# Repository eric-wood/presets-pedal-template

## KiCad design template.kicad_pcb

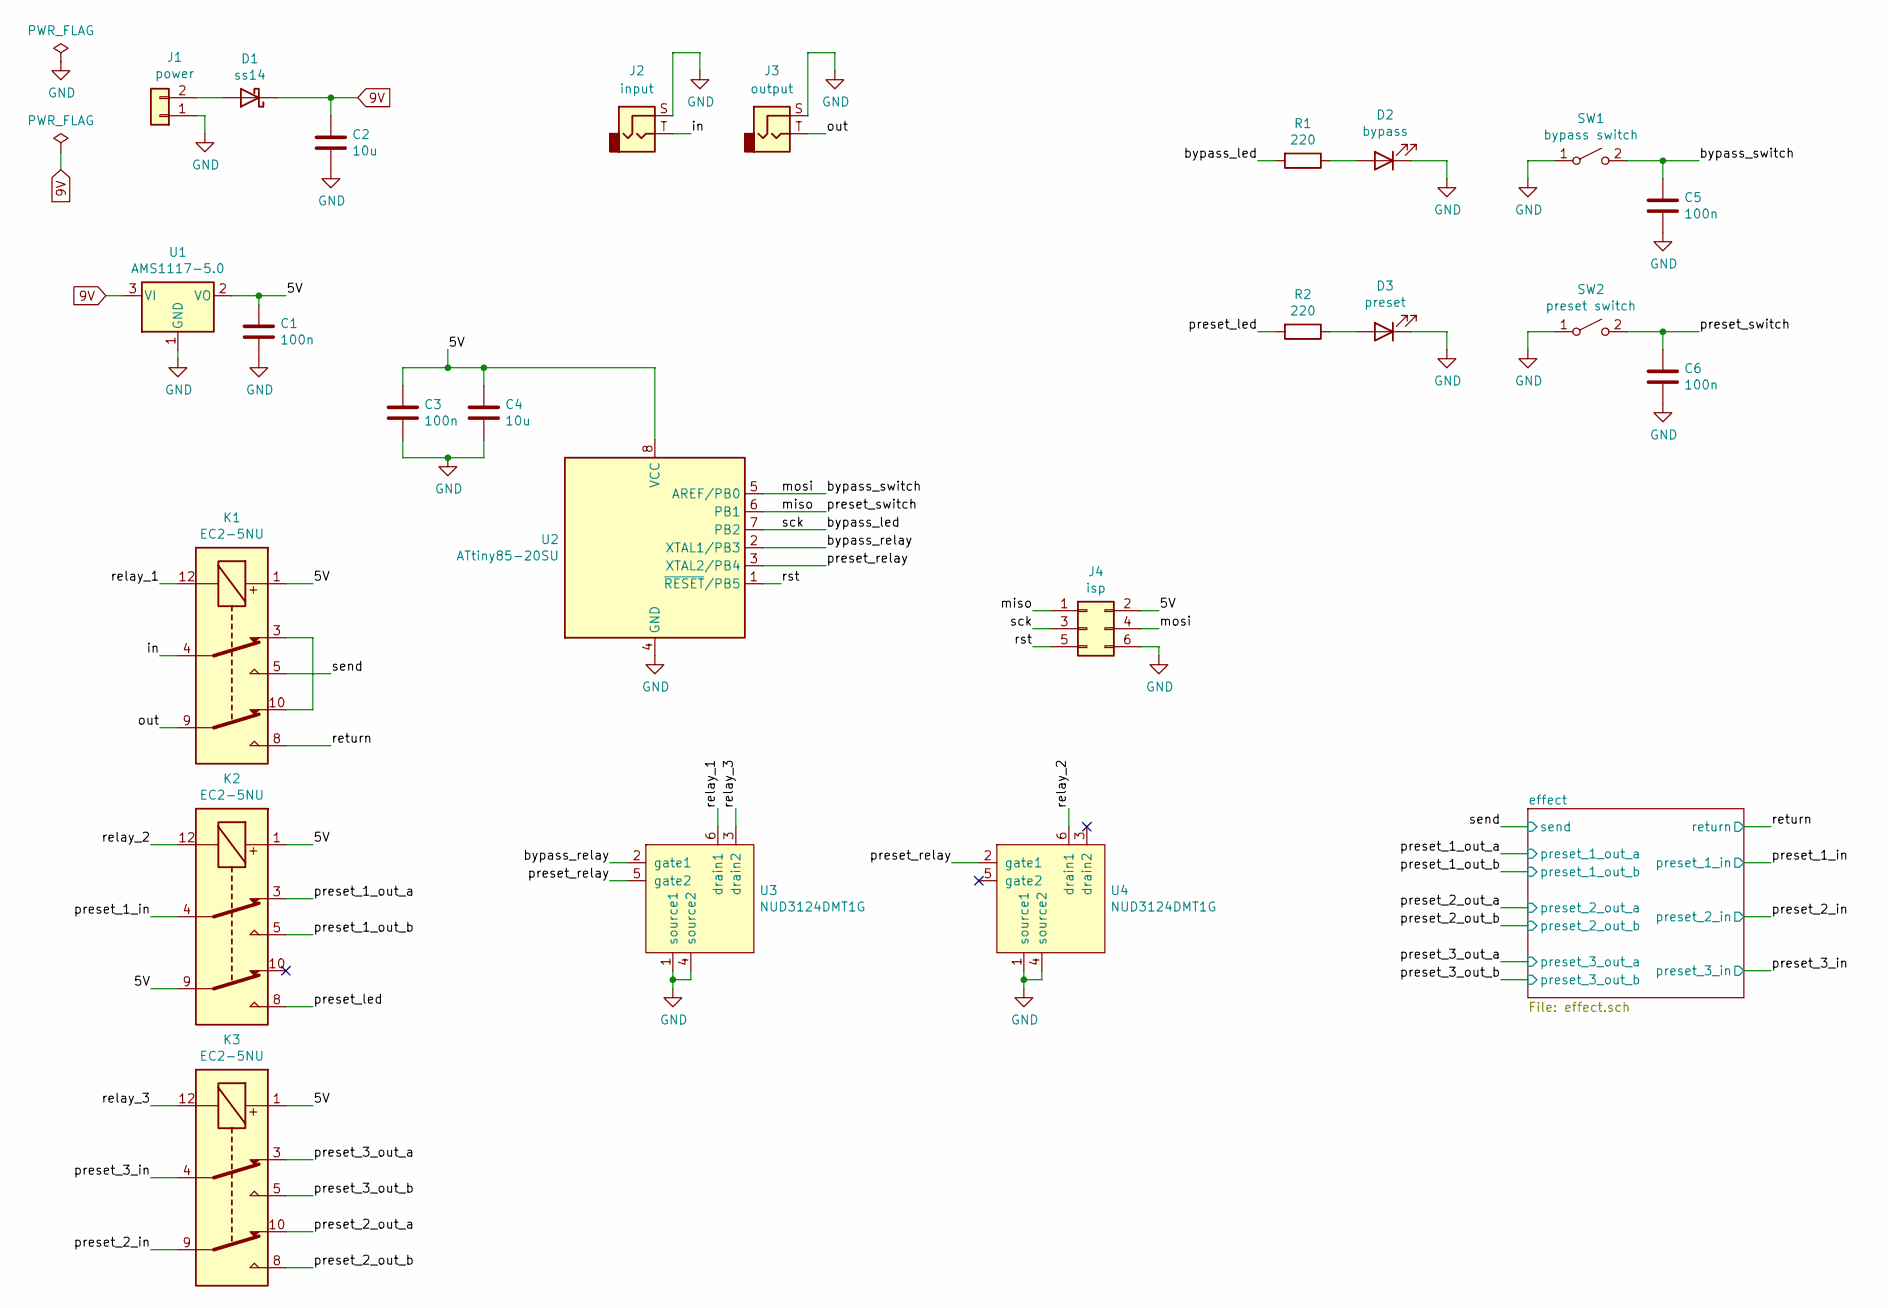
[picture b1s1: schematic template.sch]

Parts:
C1, C3, C5, C6: 100n; C_0603_1608Metric; LCSC C14663
C2, C4: 10u; C_1206_3216Metric; LCSC C13585
D1: ss14; D_SMA; LCSC C2480
D2: bypass; LED_D5.0mm_compact
D3: preset; LED_D5.0mm_compact
J1: power; PinHeader_1x02_P2.54mm_Vertical
J2: input; Jack_6.35mm_Neutrik_NMJ4HCD2_Horizontal
J3: output; Jack_6.35mm_Neutrik_NMJ4HCD2_Horizontal
J4: isp; PinHeader_2x03_P2.54mm_Vertical
K1, K2, K3: EC2-5NU; Relay_DPDT_Kemet_EC2
R1, R2: 220; R_0603_1608Metric; LCSC C22962
SW1: bypass switch; JST_XH_B2B-XH-A_1x02_P2.50mm_Vertical
SW2: preset switch; JST_XH_B2B-XH-A_1x02_P2.50mm_Vertical
U1: AMS1117-5.0; SOT-223-3_TabPin2; LCSC C6187
U2: ATtiny85-20SU; SOIJ-8_5.3x5.3mm_P1.27mm
U3, U4: NUD3124DMT1G; SC-74-6_1.5x2.9mm_P0.95mm

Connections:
9V: C2.1, D1.1 (K), U1.3 (VI); also elsewhere on the board
/5V: C1.1, C3.1, C4.1, J4.2, K1.1, K2.1, K2.9, K3.1, U1.2 (VO), U2.8 (VCC)
/bypass_led: J4.3, R1.2, U2.7 (PB2)
/bypass_relay: U2.2 (XTAL1/PB3), U3.2 (gate1)
/bypass_switch: C5.1, J4.4, SW1.2 (B), U2.5 (AREF/PB0)
/in: J2.T, K1.4
/miso: C6.1, J4.1, SW2.2 (B), U2.6 (PB1)
/out: J3.T, K1.9
/preset_1_in: K2.4; also elsewhere on the board
/preset_1_out_a: K2.3; also elsewhere on the board
/preset_1_out_b: K2.5; also elsewhere on the board
/preset_2_in: K3.9; also elsewhere on the board
/preset_2_out_a: K3.10; also elsewhere on the board
/preset_2_out_b: K3.8; also elsewhere on the board
/preset_3_in: K3.4; also elsewhere on the board
/preset_3_out_a: K3.3; also elsewhere on the board
/preset_3_out_b: K3.5; also elsewhere on the board
/preset_led: K2.8, R2.2
/preset_relay: U2.3 (XTAL2/PB4), U3.5 (gate2), U4.2 (gate1)
/relay_1: K1.12, U3.6 (drain1)
/relay_2: K2.12, U4.6 (drain1)
/relay_3: K3.12, U3.3 (drain2)
/return: K1.8; also elsewhere on the board
/rst: J4.5, U2.1 (~RESET~/PB5)
/send: K1.5; also elsewhere on the board
GND: C1.2, C2.2, C3.2, C4.2, C5.2, C6.2, D2.1 (K), D3.1 (K), J1.1, J2.S, J3.S, J4.6, SW1.1 (A), SW2.1 (A), U1.1 (GND), U2.4 (GND), U3.1 (source1), U3.4 (source2), U4.1 (source1), U4.4 (source2); also elsewhere on the board
unnamed: D1.2 (A), J1.2
unnamed: D2.2 (A), R1.1
unnamed: D3.2 (A), R2.1
unnamed: K1.3, K1.10

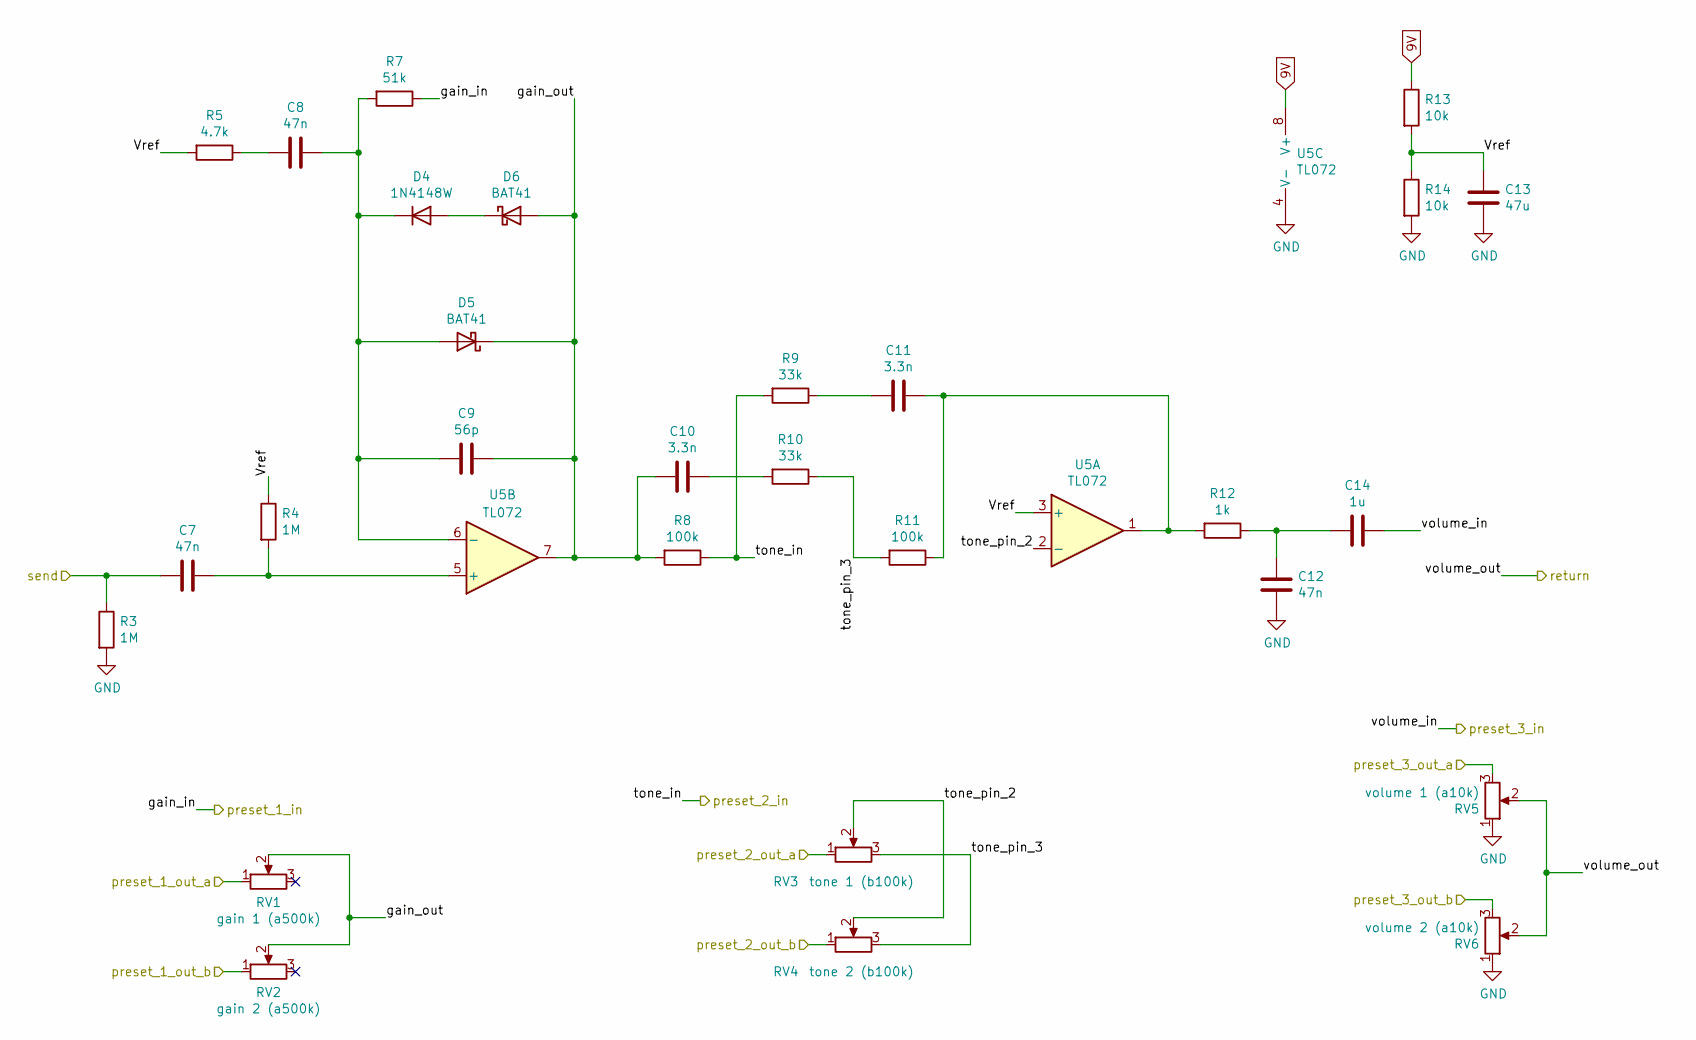
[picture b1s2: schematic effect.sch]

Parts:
C7, C8, C12: 47n; C_0603_1608Metric; LCSC C1622
C9: 56p; C_0603_1608Metric; LCSC C39148
C10, C11: 3.3n; C_0603_1608Metric; LCSC C1613
C13: 47u; C_1206_3216Metric; LCSC C96123
C14: 1u; C_0603_1608Metric; LCSC C15849
D4: 1N4148W; D_SOD-123; LCSC C81598
D5, D6: BAT41; D_DO-35_SOD27_P7.62mm_Horizontal
R3, R4: 1M; R_0603_1608Metric; LCSC C22935
R5: 4.7k; R_0603_1608Metric; LCSC C23162
R7: 51k; R_0603_1608Metric; LCSC C23196
R8, R11: 100k; R_0603_1608Metric; LCSC C25803
R9, R10: 33k; R_0603_1608Metric; LCSC C4216
R12: 1k; R_0603_1608Metric; LCSC C21190
R13, R14: 10k; R_0603_1608Metric; LCSC C25804
RV1: gain 1 (a500k); alpha_pot_16mm
RV2: gain 2 (a500k); alpha_pot_16mm
RV3: tone 1 (b100k); alpha_pot_16mm
RV4: tone 2 (b100k); alpha_pot_16mm
RV5: volume 1 (a10k); alpha_pot_16mm
RV6: volume 2 (a10k); alpha_pot_16mm
U5: TL072; SOIC-8_3.9x4.9mm_P1.27mm; LCSC C6961

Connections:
9V: R13.1, U5.8 (V+); also elsewhere on the board
/effect/Vref: C13.1, R4.1, R5.2, R13.2, R14.1, U5.3 (+)
/effect/gain_out: C9.1, C10.2, D5.1 (K), D6.2 (A), R8.2, RV1.2, RV2.2, U5.7
/effect/tone_pin_2: RV3.2, RV4.2, U5.2 (-)
/effect/tone_pin_3: R10.1, R11.2, RV3.3, RV4.3
/preset_1_in: R7.1; also elsewhere on the board
/preset_1_out_a: RV1.1; also elsewhere on the board
/preset_1_out_b: RV2.1; also elsewhere on the board
/preset_2_in: R8.1, R9.2; also elsewhere on the board
/preset_2_out_a: RV3.1; also elsewhere on the board
/preset_2_out_b: RV4.1; also elsewhere on the board
/preset_3_in: C14.1; also elsewhere on the board
/preset_3_out_a: RV5.3; also elsewhere on the board
/preset_3_out_b: RV6.3; also elsewhere on the board
/return: RV5.2, RV6.2; also elsewhere on the board
/send: C7.2, R3.1; also elsewhere on the board
GND: C12.1, C13.2, R3.2, R14.2, RV5.1, RV6.1, U5.4 (V-); also elsewhere on the board
unnamed: C7.1, R4.2, U5.5 (+)
unnamed: C8.1, C9.2, D4.1 (K), D5.2 (A), R7.2, U5.6 (-)
unnamed: C8.2, R5.1
unnamed: C10.1, R10.2
unnamed: C11.1, R11.1, R12.2, U5.1
unnamed: C11.2, R9.1
unnamed: C12.2, C14.2, R12.1
unnamed: D4.2 (A), D6.1 (K)

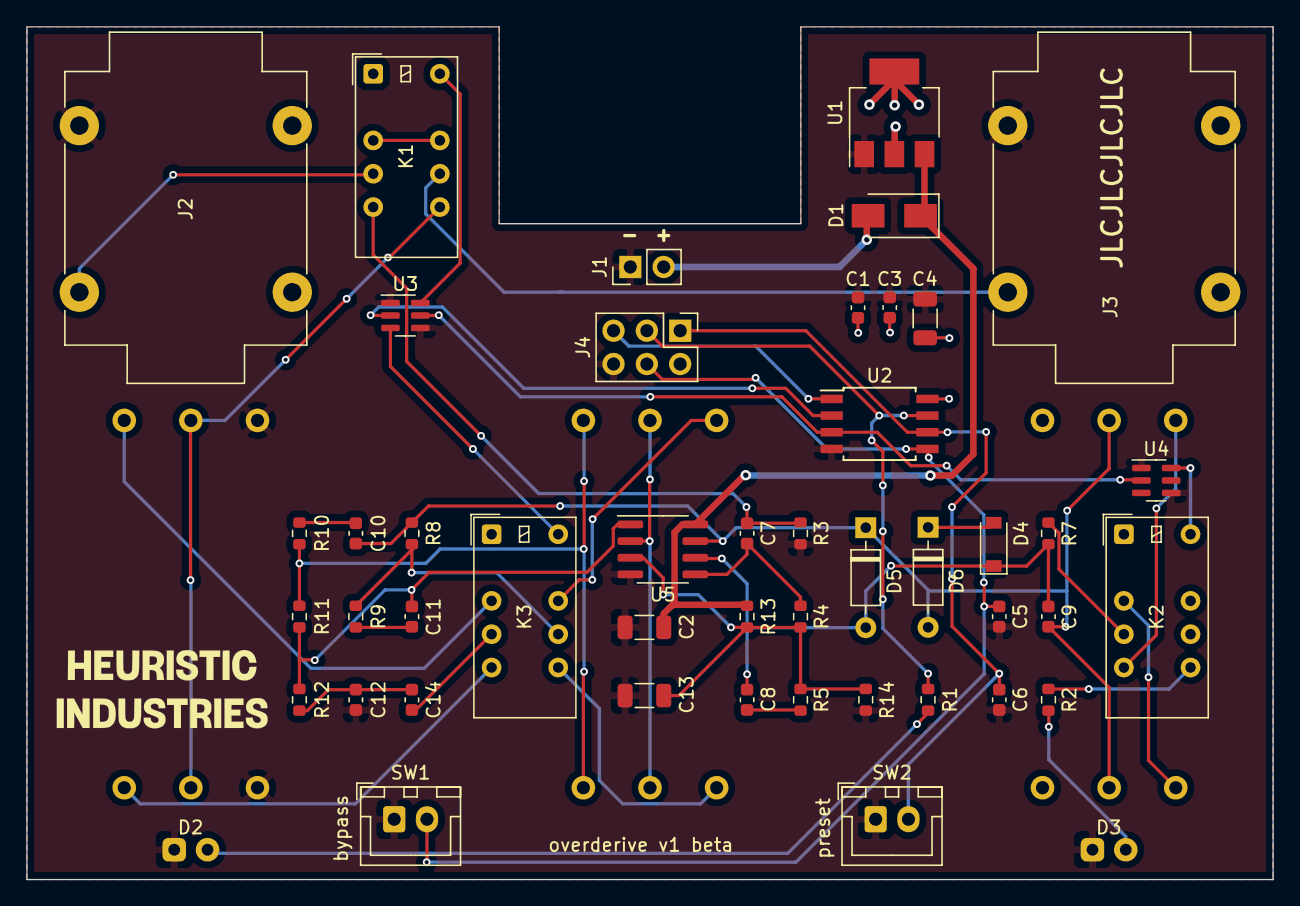
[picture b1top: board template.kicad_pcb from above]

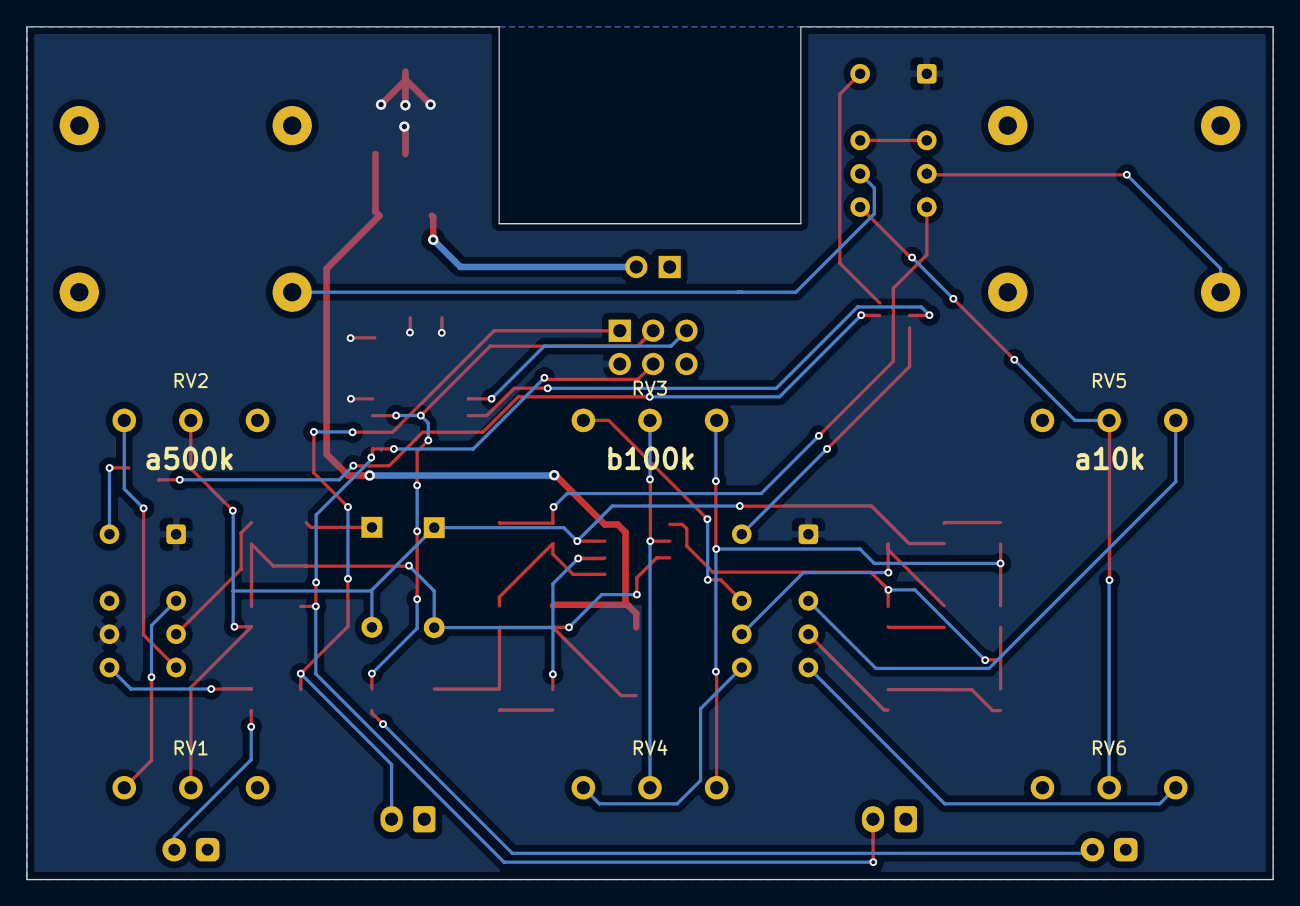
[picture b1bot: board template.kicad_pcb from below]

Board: 2 copper layers, 95.0 x 65.0 mm, 54 parts (6 on the bottom side), 42 nets.

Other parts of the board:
Ref**: Val**; logo

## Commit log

2021-05-03 LED control, programming header, switches
2021-05-04 Switch debouncing
2021-05-29 Read for review
2021-05-29 whoops
2021-05-29 Fix a few values
2021-05-29 Now with an input buffer to preserve phase
2021-05-30 Add resistor footprints/part numbers
2021-05-30 Capacitors
2021-05-30 Everything except those damn pots
2021-05-30 Added pot footprints
2021-05-30 Pot and jack positions
2021-05-31 Lots of progress
2021-05-31 Some layout improvements
2021-05-31 Is this better? Tough to say
2021-05-31 Need to start over
2021-05-31 This is better
2021-06-08 Use better schematic
2021-06-08 wooooo
2021-06-08 The orientation of these is gonna be the death of me
2021-06-08 I think I have the positioning worked out
2021-06-09 I think placement is done?
2021-06-10 so close
2021-06-11 oh yeeaaa
2021-06-12 Sent it off 2 tha fab
2021-07-20 Use solid state switching and charge pump
2021-08-02 Use 4053 switch, correct poor decisions made earlier
2021-08-03 Fix a few issues
2021-08-03 Reformatting
